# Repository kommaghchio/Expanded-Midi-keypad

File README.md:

# Expanded-Midi-keypad

The original Hack Club MIDI keypad (https://github.com/KaiPereira/MIDI-Keypad/tree/master), but with some additional features. 

Powered by a XIAO-ESP32-S3, this project creates a MIDI keypad that allows you to play individual notes on a variety of instruments, controlled by turning the rotary encoder. From there each of the 7 capacitive touch keys plays a different note. Finally, the OLED screen shows which instrument you have selected, along with a WinAMP style display. 

Schematics:

PCB Render:

BOM:
|Item                    |Qty|Supplier |Cost/item|Total Cost|link                      |
|------------------------|---|---------|---------|----------|--------------------------|
|Waveshare ESP-32-S3     |1  |RobotShop|$6.79    |$6.79     |https://www.robotshop.com/|
|EC11 Rotary Encoder     |1  |RobotShop|$3.65    |$3.65     |https://www.robotshop.com/|
|128x64 OLED             |1  |RobotShop|$3.49    |$3.49     |https://www.robotshop.com/|
|PCB                     |1  |JLCPCB   |$4.00    |$4.00     |https://jlcpcb.com/       |
|Estimated total shipping|1  |         |         |$11.89    |                          |

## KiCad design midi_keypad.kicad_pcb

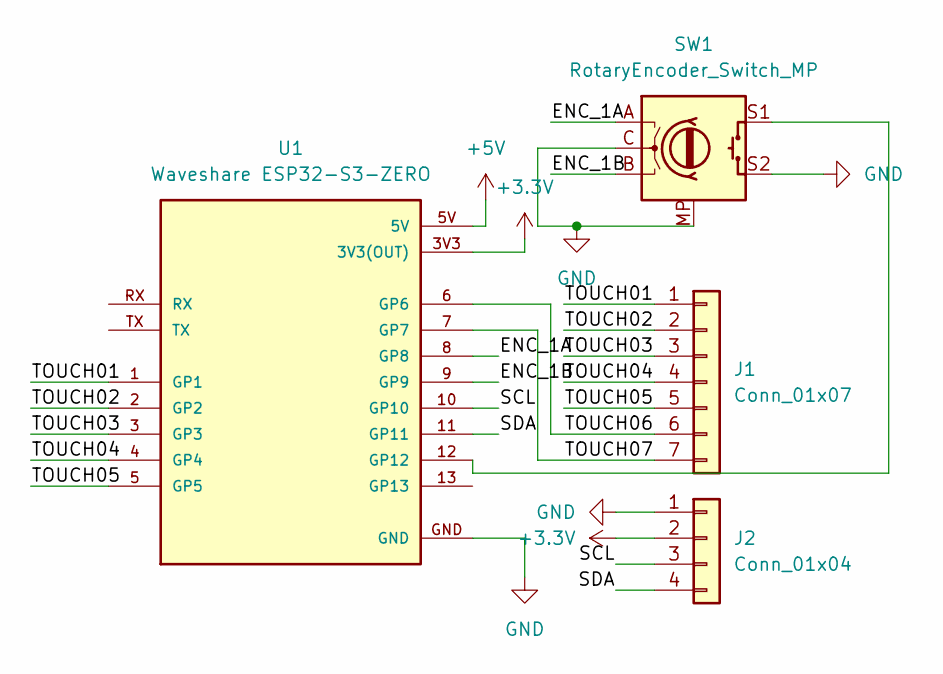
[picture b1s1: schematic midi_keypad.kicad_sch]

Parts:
J1: Conn_01x07; Capacitive Keys
J2: Conn_01x04; Display_128x64_096_I2C
SW1: RotaryEncoder_Switch_MP; RotaryEncoder_Alps_EC11E-Switch_Vertical_H20mm
U1: Waveshare ESP32-S3-ZERO; Waveshare ESP32-S3-Zero; PARTREV NA

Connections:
+3.3V: J2.2, U1.3V3 (3V3(OUT))
+5V: U1.5V
/ENC_1A: SW1.A, U1.8 (GP8)
/ENC_1B: SW1.B, U1.9 (GP9)
/SCL: J2.3, U1.10 (GP10)
/SDA: J2.4, U1.11 (GP11)
/TOUCH01: J1.1, U1.1 (GP1)
/TOUCH02: J1.2, U1.2 (GP2)
/TOUCH03: J1.3, U1.3 (GP3)
/TOUCH04: J1.4, U1.4 (GP4)
/TOUCH05: J1.5, U1.5 (GP5)
/TOUCH06: J1.6, U1.6 (GP6)
/TOUCH07: J1.7, U1.7 (GP7)
GND: J2.1, SW1.C, SW1.MP, SW1.S2, U1.GND
unnamed: SW1.S1, U1.12 (GP12)

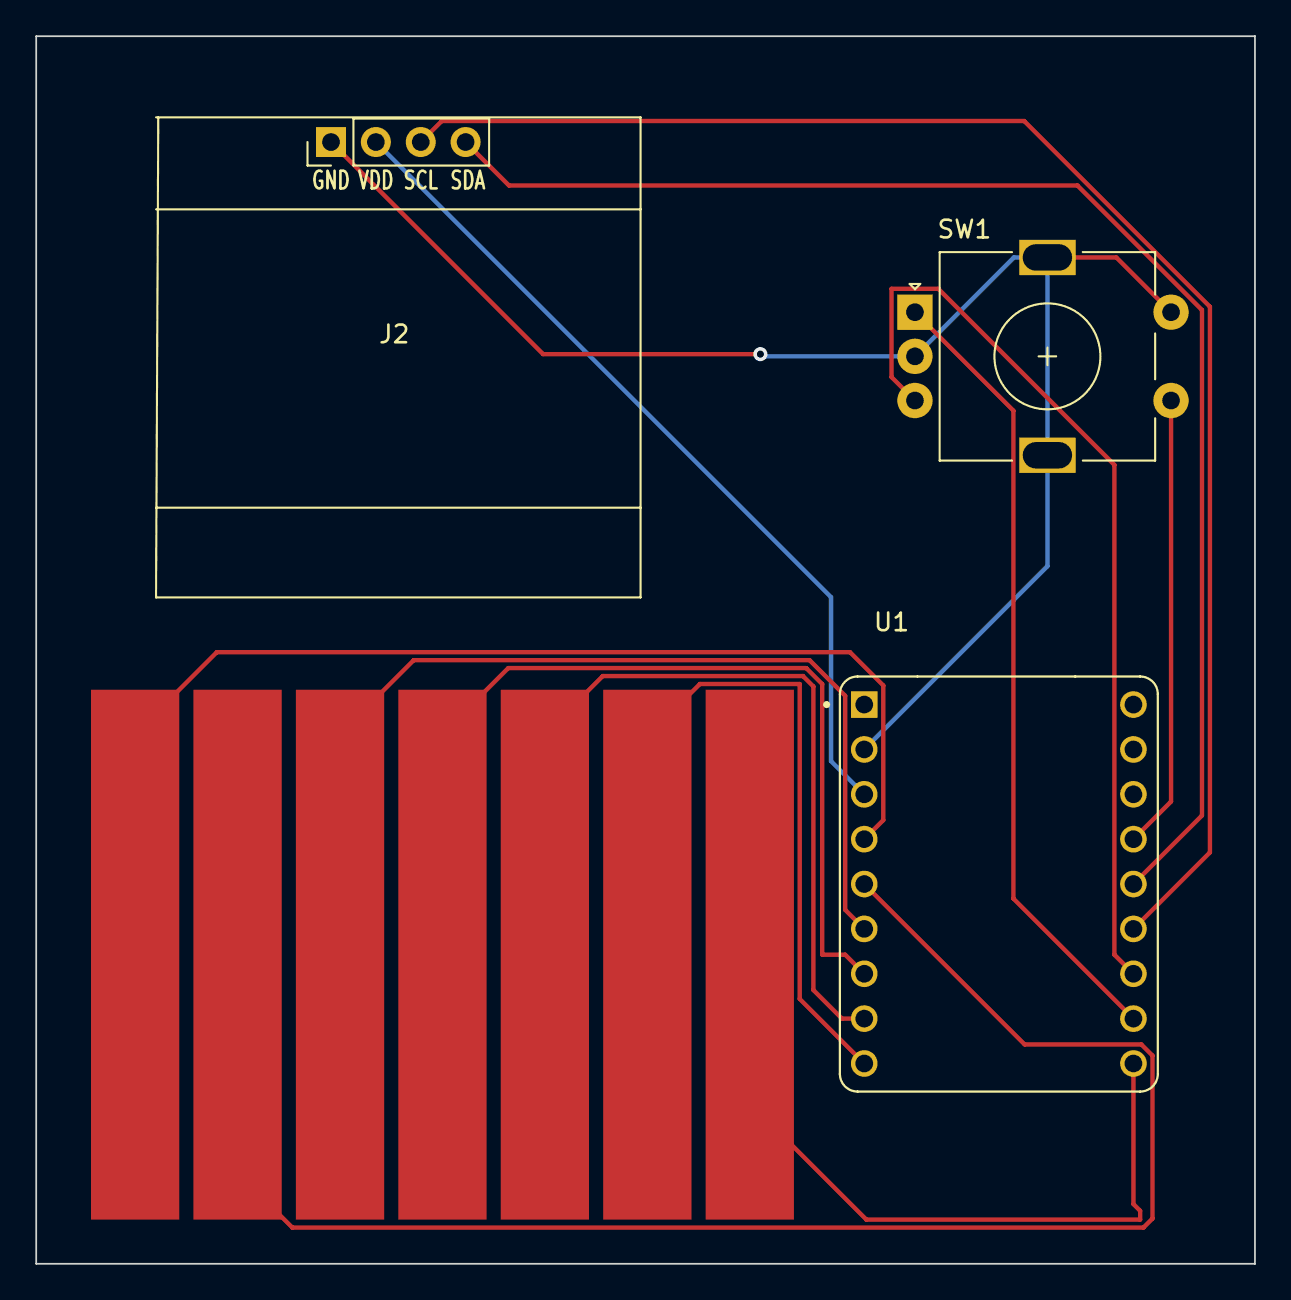
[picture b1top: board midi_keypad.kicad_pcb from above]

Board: 2 copper layers, 69.0 x 69.5 mm, 4 parts (0 on the bottom side), 14 nets.
